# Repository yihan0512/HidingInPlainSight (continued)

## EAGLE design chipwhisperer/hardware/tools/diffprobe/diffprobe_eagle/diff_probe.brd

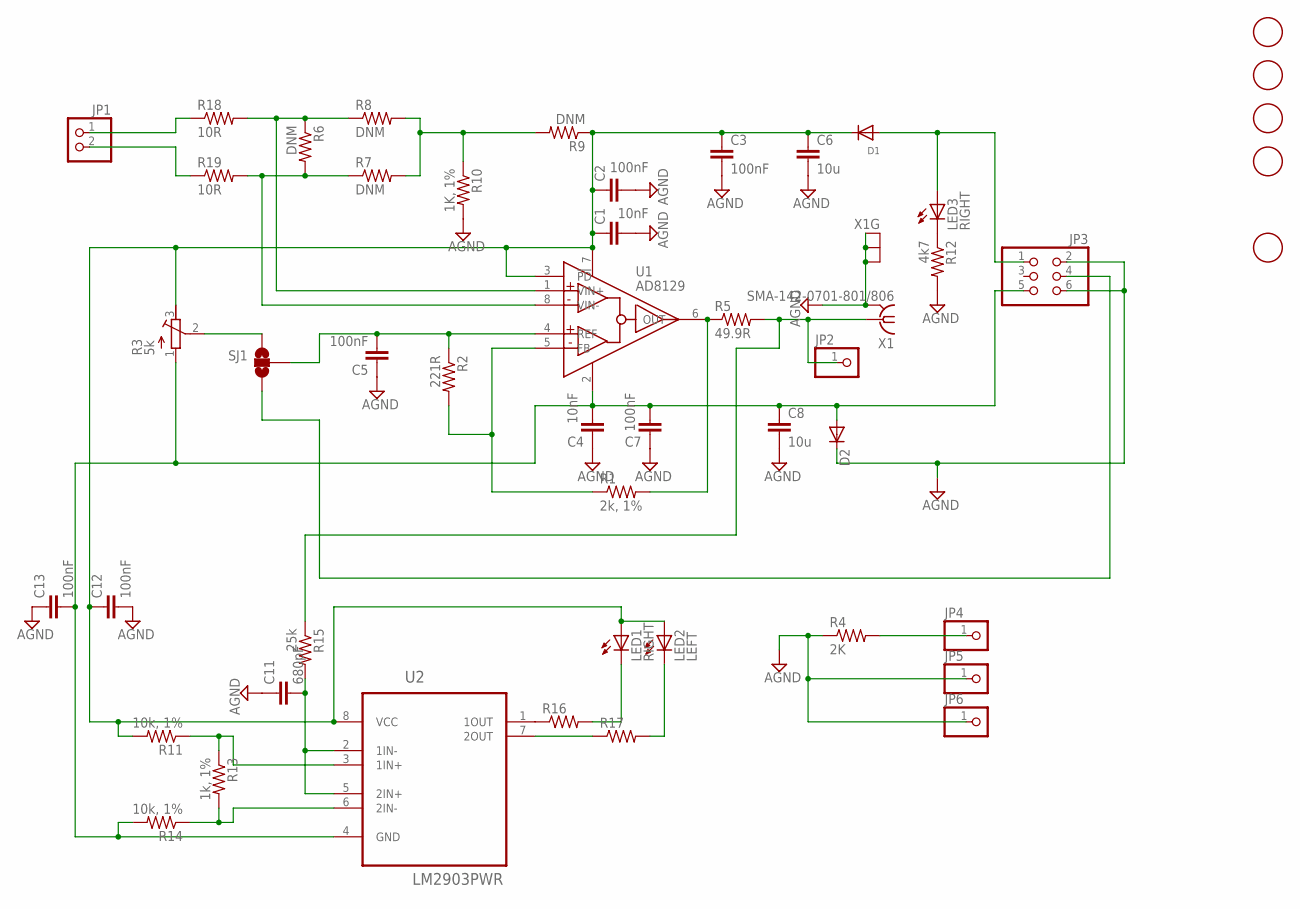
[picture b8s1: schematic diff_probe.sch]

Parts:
C1, C4: 10nF; C0603
C2, C3, C5, C7: 100nF; C0603
C6, C8: 10u; C0805
C11: 680pF; C0402
C12, C13: 100nF; C0402
D1: DIODESOD-123; SOD-123
D2: DIODE-DO-214AC; DO-214AC
FID1, FID2, FID4, FID5, FID6: FIDUCIAL; FIDUCIAL_1MM
JP1: PINHD-1X2/90; 1X02/90
JP2, JP4, JP5, JP6: PINHD-1X1; 1X01
JP3: PINHD-2X3EDGE; 6PAD_ISP
LED1, LED3: RIGHT; CHIPLED_0603
LED2: LEFT; CHIPLED_0603
R1: 2k, 1%; R0603
R2: 221R; R0603
R3: 5k; RTRIM3224J
R4: 2K; R0603
R5: 49.9R; R0603
R6: DNM; M0805
R7, R8, R9: DNM; R0603
R10: 1K, 1%; R0603
R11, R14: 10k, 1%; R0402
R12: 4k7; R0603
R13: 1k, 1%; R0402
R15: 25k; R0402
R16, R17: R-US_R0402; R0402
R18, R19: 10R; R0603
SJ1: SOLDERJUMPER_2WAYPASTE1&2; SJ_3_PASTE1&2
U1: AD8129; SO08
U2: LM2903PWR; SOP65P640X120-8N
X1: SMA-142-0701-801/806; J502-ND-142-0701-801/806

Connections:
AGND: C1.2, C2.2, C3.2, C4.1, C5.1, C6.2, C7.1, C8.2, C11.1, C12.2, C13.1, D2.C, JP3.2 (1), JP3.6 (5), JP5.1, JP6.1, R4.1, R10.2, R12.2, X1.G@1 (GND), X1.G@2 (GND), X1.G@3 (GND), X1.G@4 (GND)
unnamed: D1.A, JP3.1 (2), LED3.A
unnamed: C1.1, C2.1, C3.1, C6.1, C12.1, D1.C, LED1.A, LED2.A, R3.3 (A), R9.1, R11.2, U1.3 (!PD), U1.7 (VCC), U2.8 (VCC)
unnamed: C5.2, R2.1, SJ1.2, U1.4 (REF)
unnamed: R1.1, R2.2, U1.5 (FB)
unnamed: R1.2, R5.1, U1.6 (OUT)
unnamed: JP1.1, R18.1
unnamed: R6.1, R8.1, R18.2, U1.1 (VIN+)
unnamed: C4.2, C7.2, C8.1, C13.2, D2.A, JP3.5 (6), R3.1 (E), R14.2, U1.2 (VSS), U2.4 (GND)
unnamed: LED3.C, R12.1
unnamed: JP3.4 (3), SJ1.3
unnamed: JP4.1, R4.2
unnamed: JP2.1, R5.2, R15.1, X1.1
unnamed: R6.2, R7.1, R19.2, U1.8 (VIN-)
unnamed: JP1.2, R19.1
unnamed: R7.2, R8.2, R9.2, R10.1
unnamed: R11.1, R13.1, U2.3 (1IN+)
unnamed: R13.2, R14.1, U2.6 (2IN-)
unnamed: R16.1, U2.1 (1OUT)
unnamed: C11.2, R15.2, U2.2 (1IN-), U2.5 (2IN+)
unnamed: LED1.C, R16.2
unnamed: R17.1, U2.7 (2OUT)
unnamed: LED2.C, R17.2
unnamed: R3.2 (S), SJ1.1

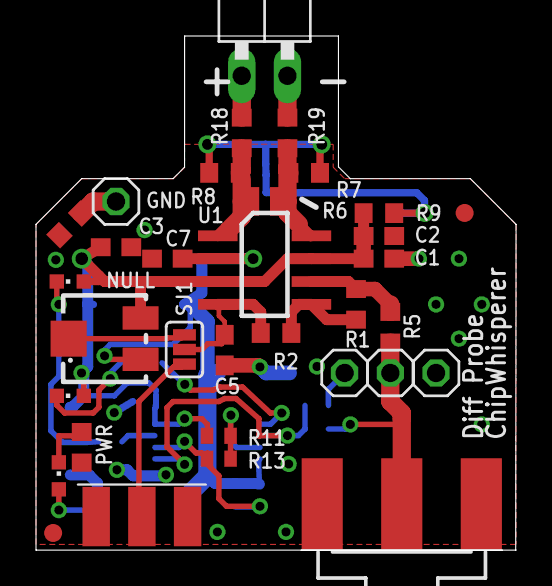
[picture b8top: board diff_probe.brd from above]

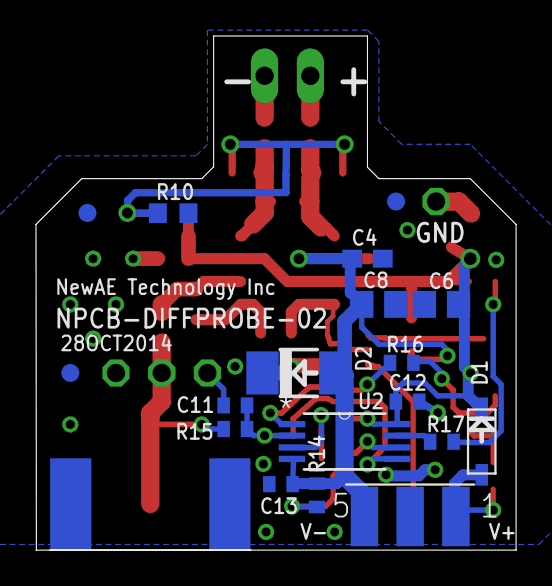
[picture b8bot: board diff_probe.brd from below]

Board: 2 copper layers, 26.7 x 28.6 mm, 50 parts (17 on the bottom side), 24 nets.

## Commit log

2021-06-28 finished cleaning code for the tcas program
2021-07-10 minor changes in readme
